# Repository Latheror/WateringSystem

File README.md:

# Watering System Project

## Overview
This project is an automated watering system for plants, featuring soil moisture monitoring, solar power management, and manual/automatic watering controls.

## Features
- **Soil Moisture Monitoring**: Real-time monitoring of soil moisture using both analog and digital sensors.
- **Automatic Watering**: Automatically activates the pump when soil moisture levels fall below a certain threshold.
- **Manual Watering**: Allows users to manually trigger a 10-second watering cycle via a web dashboard.
- **Power Management**: Monitors solar panel voltage and battery levels.
- **Web Dashboard**: A responsive web interface to view system status and control watering.

## Development Guidelines & Best Practices

### 1. Code Structure & Organization
- **Modularity**: Keep logic separated into different files (e.g., `wifi_handler.cpp`, `settings.h`).
- **Constants**: Use `settings.h` and `settings_user.h` for all hardware-specific configurations (pins, thresholds, WiFi credentials).
- **Non-blocking Code**: Avoid using `delay()` in the main loop where possible. Use `millis()` for timing-based operations (e.g., watering duration).

### 2. Hardware Abstraction
- **Relay Control**: Abstract relay operations to ensure consistent behavior (e.g., handling active-high vs. active-low modules).
- **Sensor Reading**: Standardize how sensors are read and processed before being used in logic.

### 3. Error Handling & Logging
- **Serial Debugging**: Use `Serial.println()` for critical state changes and errors.
- **Robustness**: Ensure the system can recover from WiFi disconnections or sensor failures.

### 4. Embedded C Best Practices
- **Memory Management**: Avoid dynamic memory allocation (`malloc`, `new`) to prevent memory fragmentation and leaks.
- **Data Types**: Use appropriate fixed-width integer types (e.g., `uint8_t`, `int32_t`) from `<stdint.h>`.
- **Naming Conventions**: Use clear, descriptive names for variables and functions.

## Project Structure
- `Board/`: Hardware design files.
- `Case/`: 3D model files for the enclosure.
- `Hardware/`: Component details and wiring diagrams.
- `system/`: Source code for the ESP32C3 microcontroller.

## PCB

The KiCad design files for the watering system are located in `PCB/`. These files are read and edited with KiCad 10.

### Design files

- `PCB/WateringSystem_PCB/WateringSystem_PCB.kicad_pro`: KiCad project file. It stores the KiCad project configuration and references the schematic and PCB layout.
- `PCB/WateringSystem_PCB/WateringSystem_PCB.kicad_sch`: KiCad schematic file. It describes the components, symbols, power rails, nets, and logical connections.
- `PCB/WateringSystem_PCB/WateringSystem_PCB.kicad_pcb`: KiCad PCB board file. It contains the board outline, footprints, copper tracks, vias, zones, and silkscreen.
- `PCB/WateringSystem_PCB/fp-lib-table`: KiCad footprint-library table. It tells KiCad where to find the custom and external footprint libraries used by the board.

### Custom libraries

- `PCB/ESP32-C3_SuperMini.kicad_sym`: Custom KiCad symbol-library file containing the ESP32-C3 SuperMini symbol used by the schematic.
- `PCB/General.kicad_sym`: Custom KiCad symbol-library file containing additional project-specific schematic symbols.
- `PCB/WateringSystem_PCB/ESP32-C3_SuperMini.pretty/ESP32-C3_SuperMini.kicad_mod`: Custom KiCad footprint file for the ESP32-C3 SuperMini module.

### Konnect configuration

- `PCB/WateringSystem_PCB/.konnect/project.json`: Project-specific KiCad/Konnect configuration, including design rules and fabrication preferences. Keep it versioned when those shared project settings are expected to be reproducible.

Generated Gerbers, drill files, ERC reports, backups, lock files, KiCad local preferences, and history files are intentionally excluded by `.gitignore`. They can be regenerated from the versioned design sources when needed.

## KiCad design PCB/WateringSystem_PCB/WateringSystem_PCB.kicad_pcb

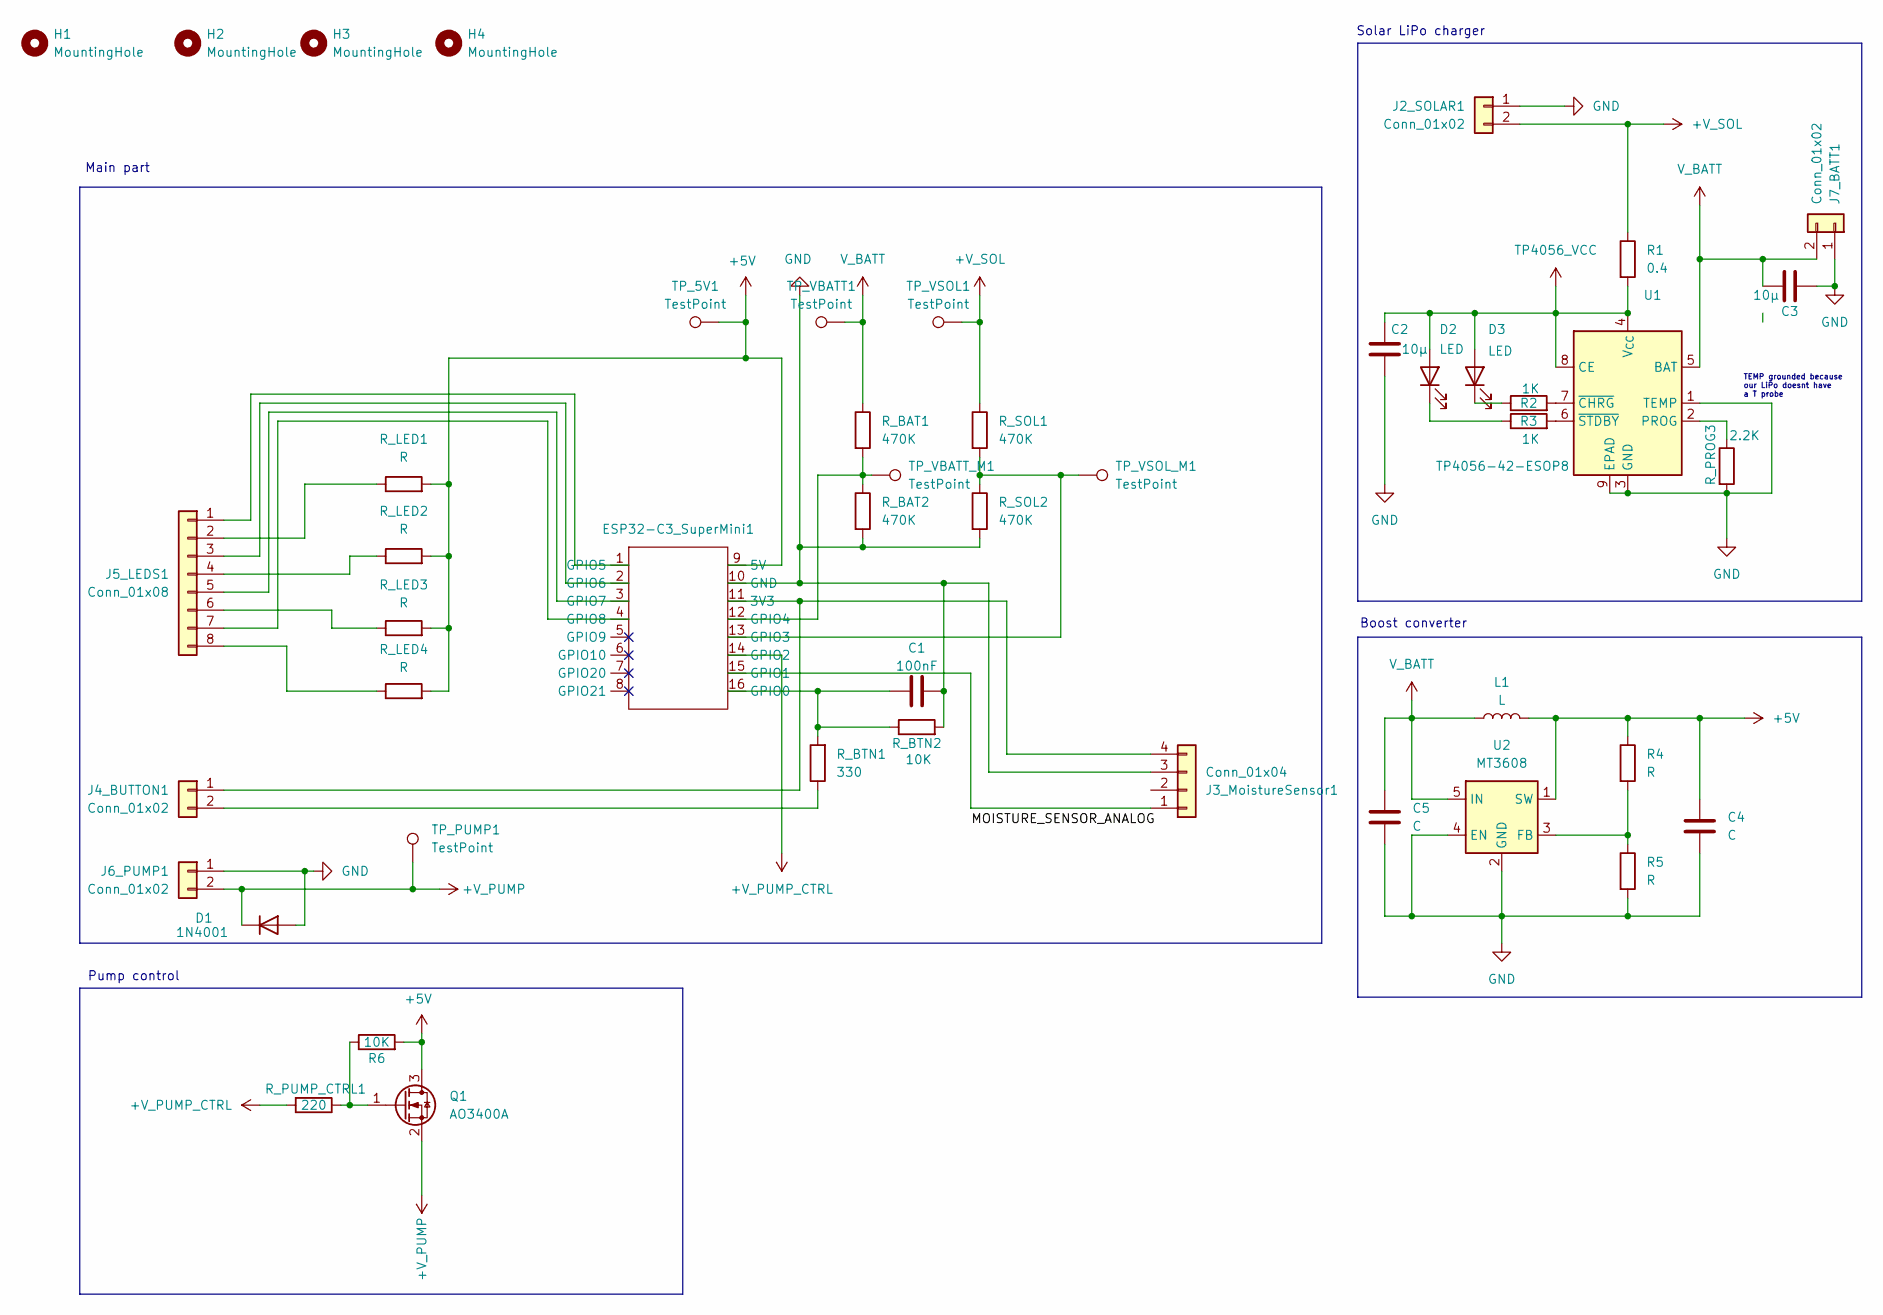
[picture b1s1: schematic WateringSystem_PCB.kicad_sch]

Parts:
C1: 100nF; CP_Radial_D4.0mm_P1.50mm
C2, C3: 10µ; C_1206_3216Metric_Pad1.33x1.80mm_HandSolder
C4, C5: C; C_1206_3216Metric_Pad1.33x1.80mm_HandSolder
D1: 1N4001; D_DO-41_SOD81_P10.16mm_Horizontal
D2, D3: LED; LED_1206_3216Metric_Pad1.42x1.75mm_HandSolder
ESP32-C3_SuperMini1: ESP32-C3_SuperMini
H1, H2, H3, H4: MountingHole; MountingHole_3.2mm_M3
J2_SOLAR1, J4_BUTTON1, J6_PUMP1, J7_BATT1: Conn_01x02; JST_XH_B2B-XH-A_1x02_P2.50mm_Vertical
J3_MoistureSensor1: Conn_01x04; JST_XH_B4B-XH-A_1x04_P2.50mm_Vertical
J5_LEDS1: Conn_01x08; JST_XH_B8B-XH-A_1x08_P2.50mm_Vertical
L1: L; L_Coilcraft_LPS4018
Q1: AO3400A; SOT-23
R1: 0.4; R_1206_3216Metric_Pad1.30x1.75mm_HandSolder
R2, R3: 1K; R_1206_3216Metric_Pad1.30x1.75mm_HandSolder
R4, R5: R; R_1206_3216Metric_Pad1.30x1.75mm_HandSolder
R6: 10K; R_1206_3216Metric_Pad1.30x1.75mm_HandSolder
R_BAT1, R_BAT2: 470K; R_1206_3216Metric_Pad1.30x1.75mm_HandSolder
R_BTN1: 330; R_1206_3216Metric_Pad1.30x1.75mm_HandSolder
R_BTN2: 10K; R_1206_3216Metric_Pad1.30x1.75mm_HandSolder
R_LED1, R_LED2, R_LED3, R_LED4: R; R_1206_3216Metric_Pad1.30x1.75mm_HandSolder
R_PROG3: 2.2K; R_1206_3216Metric_Pad1.30x1.75mm_HandSolder
R_PUMP_CTRL1: 220; R_1206_3216Metric_Pad1.30x1.75mm_HandSolder
R_SOL1, R_SOL2: 470K; R_1206_3216Metric_Pad1.30x1.75mm_HandSolder
TP_5V1: TestPoint; TestPoint_Pad_1.0x1.0mm
TP_PUMP1: TestPoint; TestPoint_Pad_1.0x1.0mm
TP_VBATT1: TestPoint; TestPoint_Pad_1.0x1.0mm
TP_VBATT_M1: TestPoint; TestPoint_Pad_1.0x1.0mm
TP_VSOL1: TestPoint; TestPoint_Pad_1.0x1.0mm
TP_VSOL_M1: TestPoint; TestPoint_Pad_1.0x1.0mm
U1: TP4056-42-ESOP8; SOIC-8-1EP_3.9x4.9mm_P1.27mm_EP2.29x3mm
U2: MT3608; SOT-23-6

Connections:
+5V: C4.1, ESP32-C3_SuperMini1.9 (5V), L1.2, Q1.3 (D), R4.1, R6.2, R_LED1.2, R_LED2.2, R_LED3.2, R_LED4.2, TP_5V1.1 (1_1), U2.1 (SW)
+V_PUMP: D1.1 (K), J6_PUMP1.2, Q1.2 (S), TP_PUMP1.1 (1_1)
+V_PUMP_CTRL: ESP32-C3_SuperMini1.14 (GPIO2), R_PUMP_CTRL1.2
+V_SOL: J2_SOLAR1.2, R1.1, R_SOL1.1, TP_VSOL1.1 (1_1)
GND: C1.2, C2.2, C3.2, C4.2, C5.2, D1.2 (A), ESP32-C3_SuperMini1.10 (GND), J2_SOLAR1.1, J3_MoistureSensor1.3, J6_PUMP1.1, J7_BATT1.1, R5.2, R_BAT2.2, R_BTN2.2, R_PROG3.2, R_SOL2.2, U1.1 (TEMP), U1.3 (GND), U1.9 (EPAD), U2.2 (GND), U2.4 (EN)
unnamed: D2.1 (K), R3.1
unnamed: D3.1 (K), R2.1
unnamed: ESP32-C3_SuperMini1.11 (3V3), J3_MoistureSensor1.4, J4_BUTTON1.1
unnamed: C1.1, ESP32-C3_SuperMini1.16 (GPIO0), R_BTN1.2, R_BTN2.1
unnamed: ESP32-C3_SuperMini1.15 (GPIO1), J3_MoistureSensor1.1
unnamed: ESP32-C3_SuperMini1.13 (GPIO3), R_SOL1.2, R_SOL2.1, TP_VSOL_M1.1 (1_1)
unnamed: ESP32-C3_SuperMini1.12 (GPIO4), R_BAT1.2, R_BAT2.1, TP_VBATT_M1.1 (1_1)
unnamed: ESP32-C3_SuperMini1.1 (GPIO5), J5_LEDS1.1
unnamed: ESP32-C3_SuperMini1.2 (GPIO6), J5_LEDS1.3
unnamed: ESP32-C3_SuperMini1.3 (GPIO7), J5_LEDS1.5
unnamed: ESP32-C3_SuperMini1.4 (GPIO8), J5_LEDS1.7
unnamed: J4_BUTTON1.2, R_BTN1.1
unnamed: J5_LEDS1.2, R_LED1.1
unnamed: J5_LEDS1.4, R_LED2.1
unnamed: J5_LEDS1.6, R_LED3.1
unnamed: J5_LEDS1.8, R_LED4.1
unnamed: Q1.1 (G), R6.1, R_PUMP_CTRL1.1
unnamed: R_PROG3.1, U1.2 (PROG)
unnamed: R2.2, U1.7 (~CHRG)
unnamed: R3.2, U1.6 (~STDBY)
unnamed: R4.2, R5.1, U2.3 (FB)
TP4056_VCC: C2.1, D2.2 (A), D3.2 (A), R1.2, U1.4 (V_{CC}), U1.8 (CE)
V_BATT: C3.1, C5.1, J7_BATT1.2, L1.1, R_BAT1.1, TP_VBATT1.1 (1_1), U1.5 (BAT), U2.5 (IN)

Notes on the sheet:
Boost converter
Solar LiPo charger
Pump control
Main part
TEMP grounded because our LiPo doesnt have a T probe

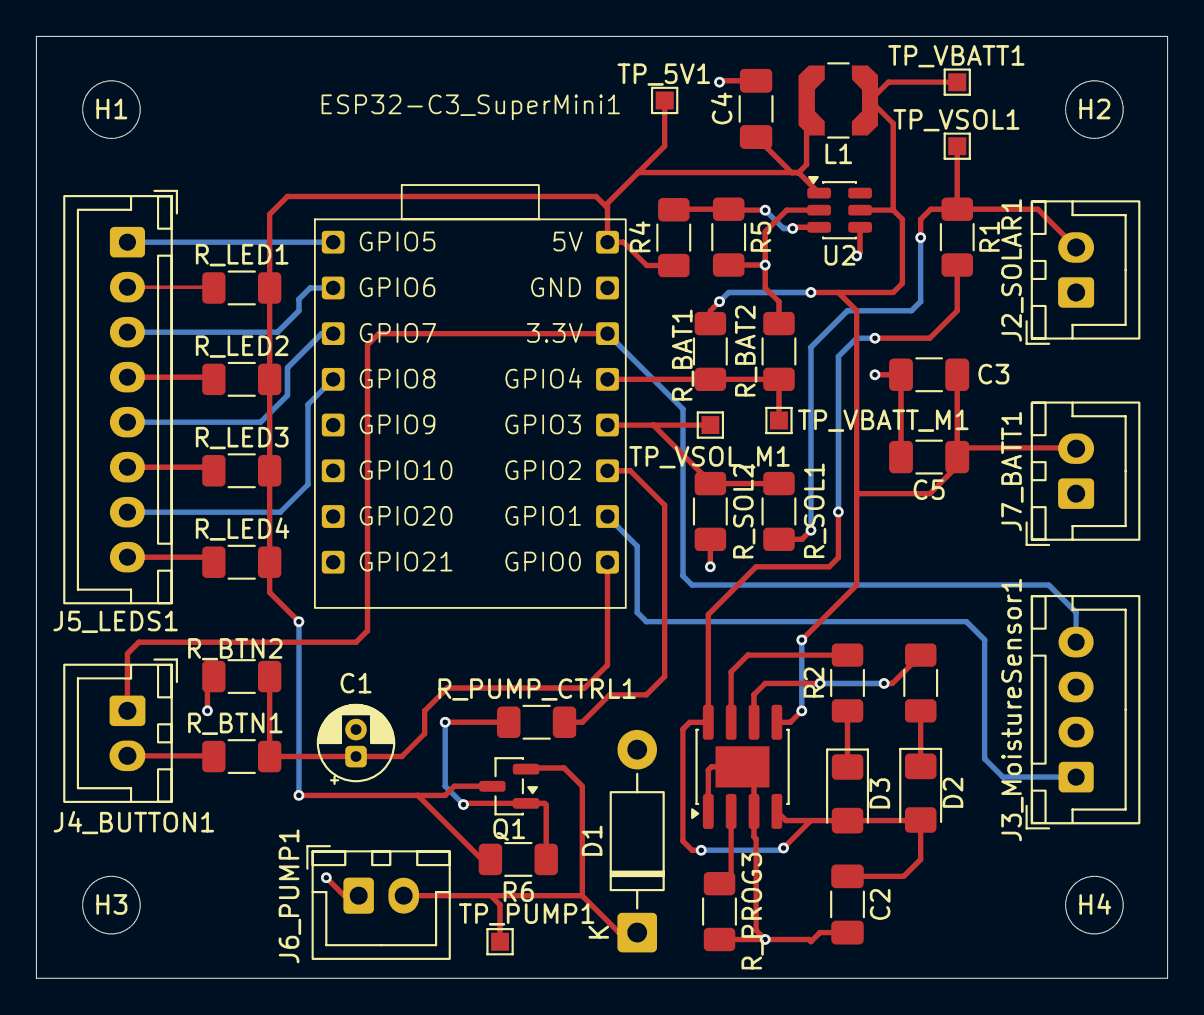
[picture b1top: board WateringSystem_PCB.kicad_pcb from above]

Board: 2 copper layers, 62.8 x 52.3 mm, 47 parts (0 on the bottom side), 28 nets.

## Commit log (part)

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2026-03-16 Add board pinout image
2026-03-16 Write demo code to blink led
2026-03-16 Start wifi code
2026-03-16 Move led pin define
2026-03-16 Add a screenshot of arduino settings for board.
2026-03-16 Clean and document code.
2026-06-07 Read moisture sensor value. Move wifi credentials into a new "user settings" file.
2026-06-07 Control relay
2026-06-18 Add hardware documentation and 3d plan files
2026-06-24 Serve a webapp to control the system
2026-06-24 Reorganize pumping code;
2026-06-25 Move webapp code into dedicated files.
2026-06-25 Change color
2026-06-25 Reorganize watering state.
2026-06-25 Add emojis and styles
2026-06-28 Minor web page modifs
2026-06-28 Create a sensor class.
2026-06-28 Create a VoltageSensor class
2026-06-28 Improve moisture
2026-06-28 Refresh page every second.
2026-06-28 Improve webpapp code
